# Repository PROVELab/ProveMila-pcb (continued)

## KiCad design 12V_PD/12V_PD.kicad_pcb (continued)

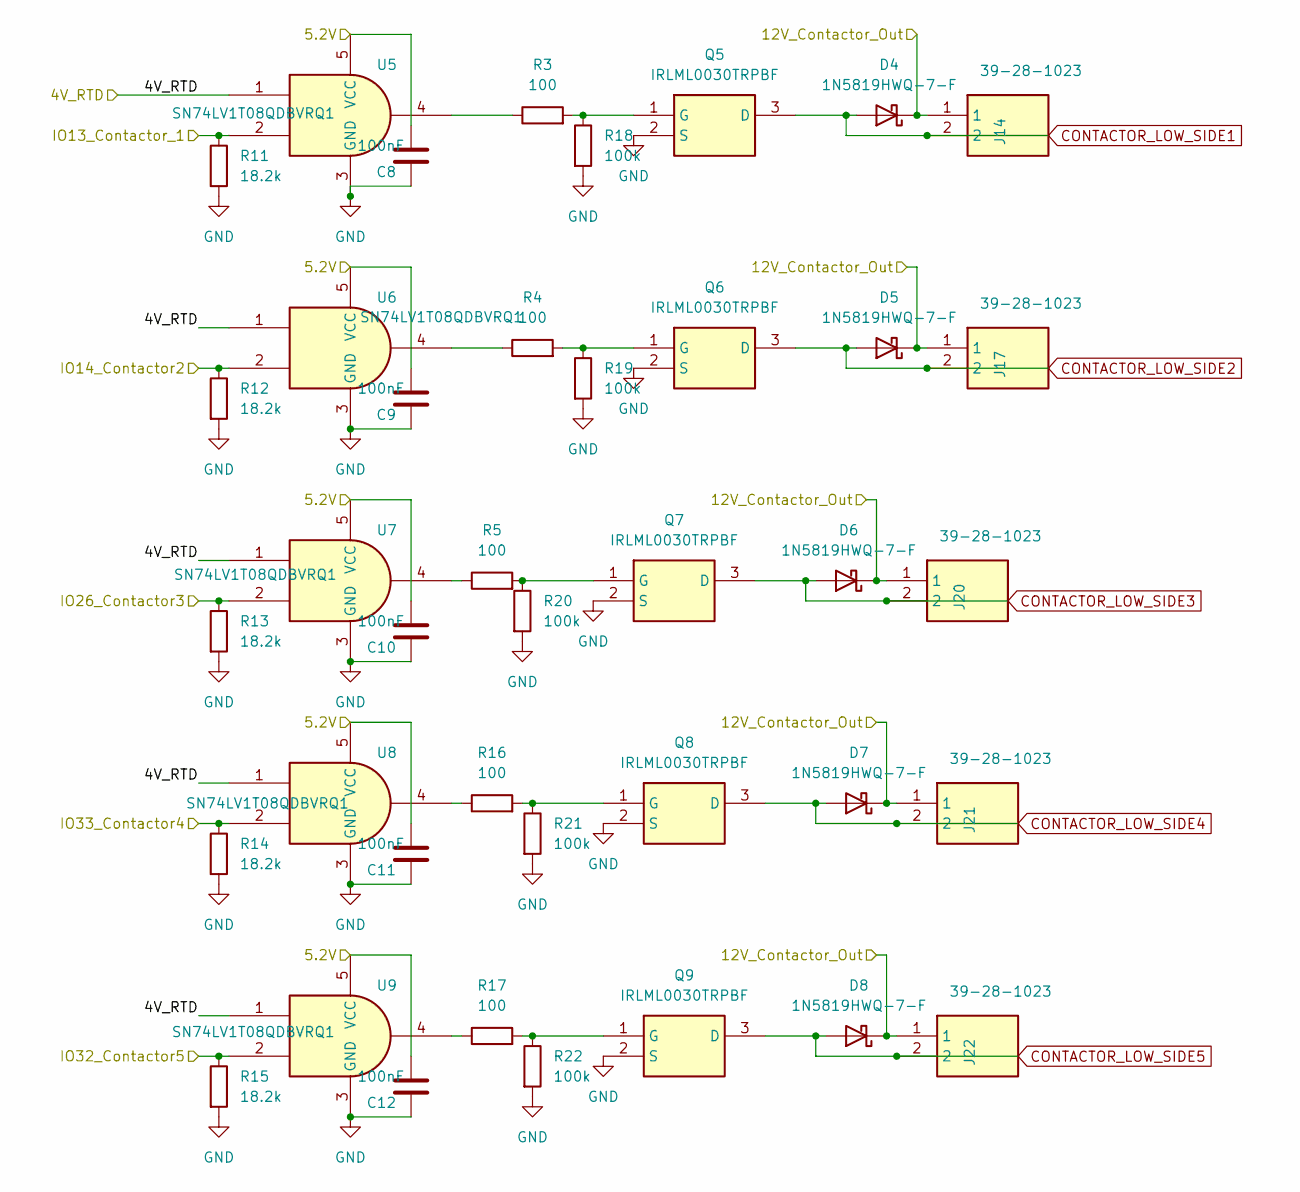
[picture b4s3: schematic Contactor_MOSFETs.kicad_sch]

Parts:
C8, C9, C10, C11, C12: 100nF; C_0805_2012Metric_Pad1.18x1.45mm_HandSolder
D4, D5, D6, D7, D8: 1N5819HWQ-7-F; D_SOD-123
J14, J17, J20, J21, J22: 39-28-1023; Mouser Part Number 538-39-28-1023
Q5, Q6, Q7, Q8, Q9: IRLML0030TRPBF; SOT-23-3; Mouser Part Number 942-IRLML0030TRPBF
R3, R4, R5, R16, R17: 100; R_0805_2012Metric_Pad1.20x1.40mm_HandSolder
R11, R12, R13, R14, R15: 18.2k; R_0805_2012Metric_Pad1.20x1.40mm_HandSolder
R18, R19, R20, R21, R22: 100k; R_0805_2012Metric_Pad1.20x1.40mm_HandSolder
U5, U6, U7, U8, U9: SN74LV1T08QDBVRQ1; SOT-23-5_HandSoldering

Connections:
/4V_RTD: U5.1, U6.1, U7.1, U8.1, U9.1; also elsewhere on the board
/12V: D4.1 (K), D5.1 (K), D6.1 (K), D7.1 (K), D8.1 (K), J14.1, J17.1, J20.1, J21.1, J22.1; also elsewhere on the board
/BUCK_5V: C8.1, C9.1, C10.1, C11.1, C12.1, U5.5 (VCC), U6.5 (VCC), U7.5 (VCC), U8.5 (VCC), U9.5 (VCC); also elsewhere on the board
/Contactor_MOSFETs/IO13_Contactor_1: R11.1, U5.2; also elsewhere on the board
/Contactor_MOSFETs/IO14_Contactor2: R12.1, U6.2; also elsewhere on the board
/Contactor_MOSFETs/IO26_Contactor3: R13.1, U7.2; also elsewhere on the board
/Contactor_MOSFETs/IO32_Contactor5: R15.1, U9.2; also elsewhere on the board
/Contactor_MOSFETs/IO33_Contactor4: R14.1, U8.2; also elsewhere on the board
CONTACTOR_LOW_SIDE1: D4.2 (A), J14.2, Q5.3 (D)
CONTACTOR_LOW_SIDE2: D5.2 (A), J17.2, Q6.3 (D)
CONTACTOR_LOW_SIDE3: D6.2 (A), J20.2, Q7.3 (D)
CONTACTOR_LOW_SIDE4: D7.2 (A), J21.2, Q8.3 (D)
CONTACTOR_LOW_SIDE5: D8.2 (A), J22.2, Q9.3 (D)
GND: C8.2, C9.2, C10.2, C11.2, C12.2, Q5.2 (S), Q6.2 (S), Q7.2 (S), Q8.2 (S), Q9.2 (S), R11.2, R12.2, R13.2, R14.2, R15.2, R18.2, R19.2, R20.2, R21.2, R22.2, U5.3 (GND), U6.3 (GND), U7.3 (GND), U8.3 (GND), U9.3 (GND); also elsewhere on the board
unnamed: Q5.1 (G), R3.2, R18.1
unnamed: Q6.1 (G), R4.2, R19.1
unnamed: Q7.1 (G), R5.2, R20.1
unnamed: Q8.1 (G), R16.2, R21.1
unnamed: Q9.1 (G), R17.2, R22.1
unnamed: R3.1, U5.4
unnamed: R4.1, U6.4
unnamed: R5.1, U7.4
unnamed: R16.1, U8.4
unnamed: R17.1, U9.4

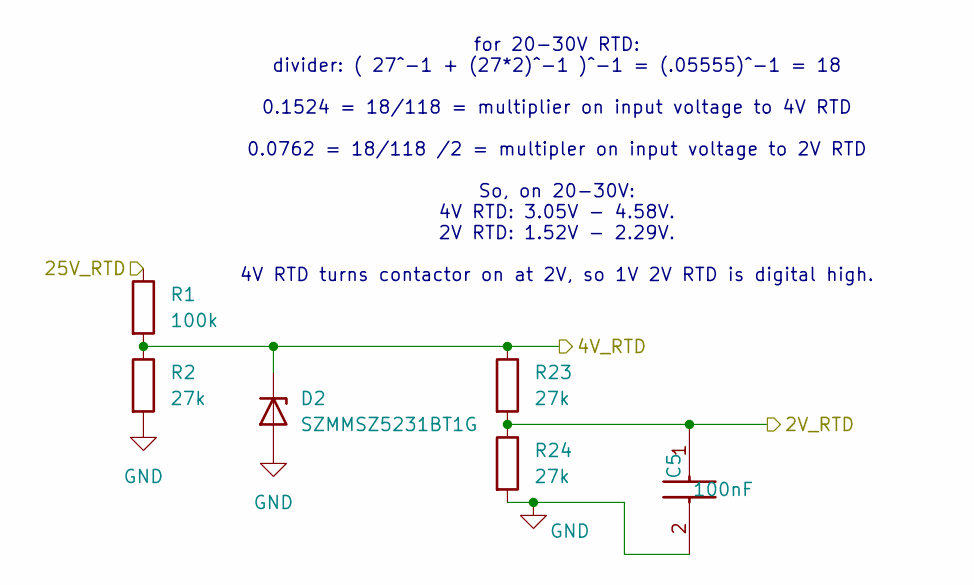
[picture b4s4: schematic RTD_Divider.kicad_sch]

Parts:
C5: 100nF; C_0805_2012Metric_Pad1.18x1.45mm_HandSolder
D2: SZMMSZ5231BT1G; D_SOD-123
R1: 100k; R_0805_2012Metric_Pad1.20x1.40mm_HandSolder
R2, R23, R24: 27k; R_0805_2012Metric_Pad1.20x1.40mm_HandSolder

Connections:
/4V_RTD: D2.1 (K), R1.2, R2.1, R23.1; also elsewhere on the board
/25V_RTD: R1.1; also elsewhere on the board
/RTD_Divider/2V_RTD: C5.1, R23.2, R24.1; also elsewhere on the board
GND: C5.2, D2.2 (A), R2.2, R24.2; also elsewhere on the board

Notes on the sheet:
for 20-30V RTD: divider: ( 27^-1 + (27*2)^-1 )^-1 = (.05555)^-1 = 18 0.1524 = 18/118 = multiplier on input voltage to 4V RTD 0.0762 = 18/118 /2 = multipler on input voltage to 2V RTD So, on 20-30V: 4V RTD: 3.05V - 4.58V. 2V RTD: 1.52V - 2.29V. 4V RTD turns contactor on at 2V, so 1V 2V RTD is digita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

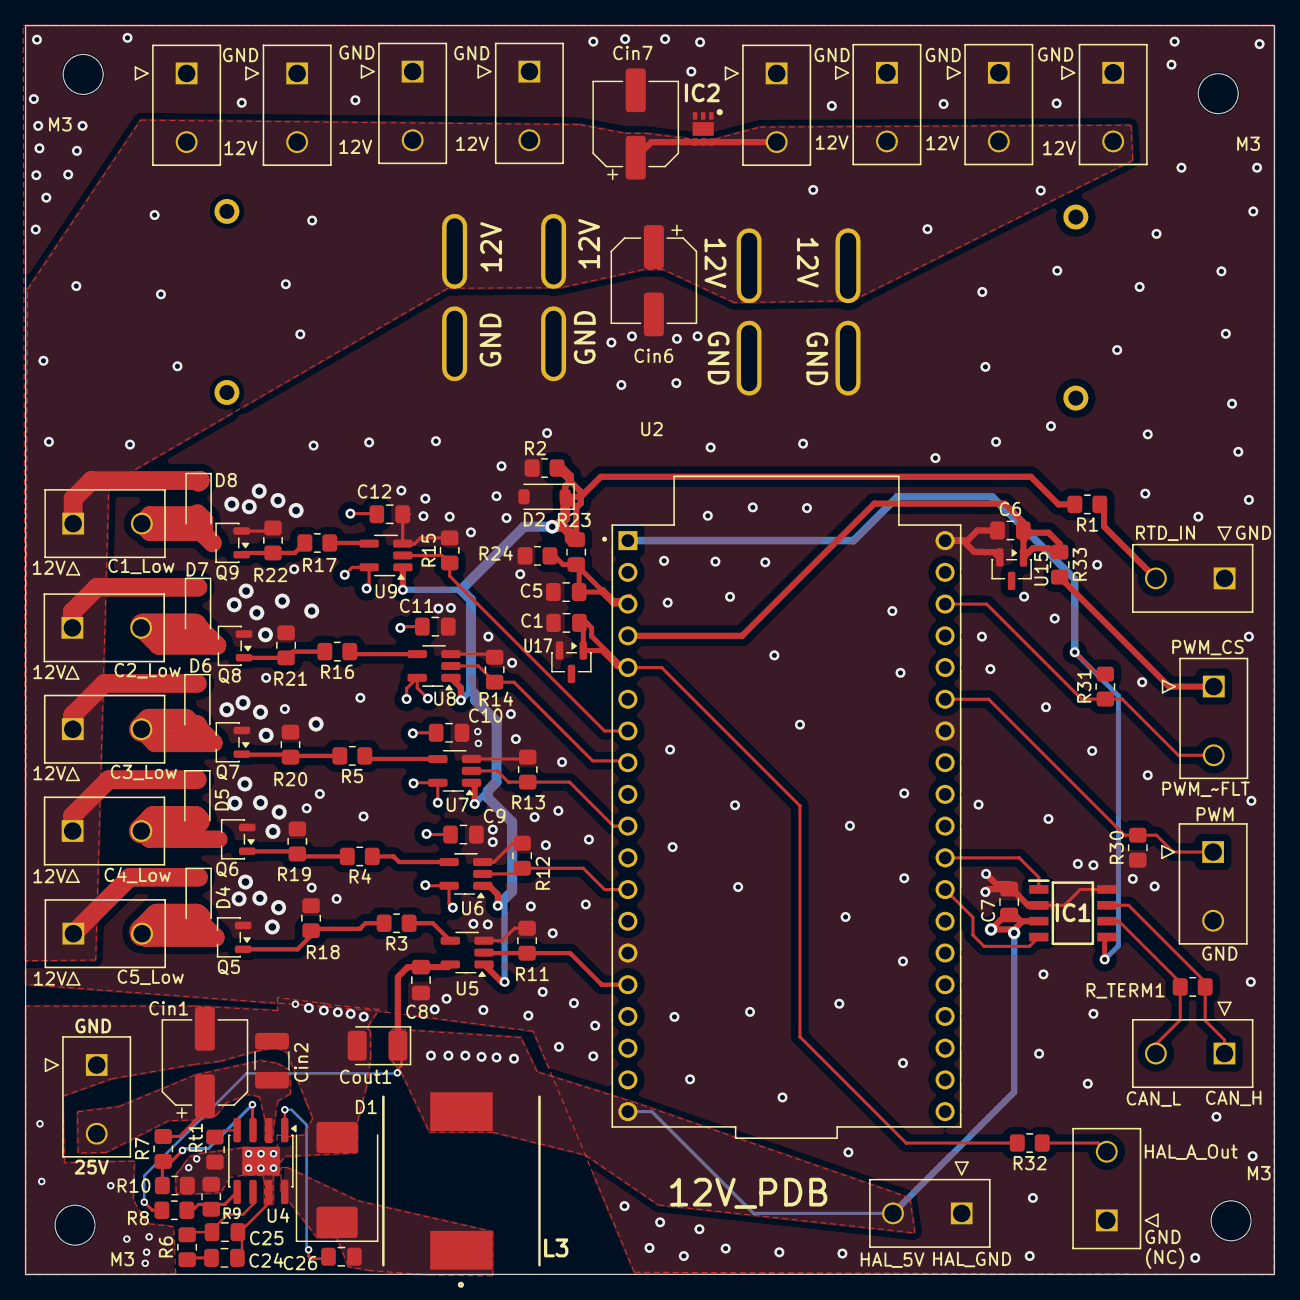
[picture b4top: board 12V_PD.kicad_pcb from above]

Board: 4 copper layers, 100.0 x 100.0 mm, 97 parts (0 on the bottom side), 45 nets.

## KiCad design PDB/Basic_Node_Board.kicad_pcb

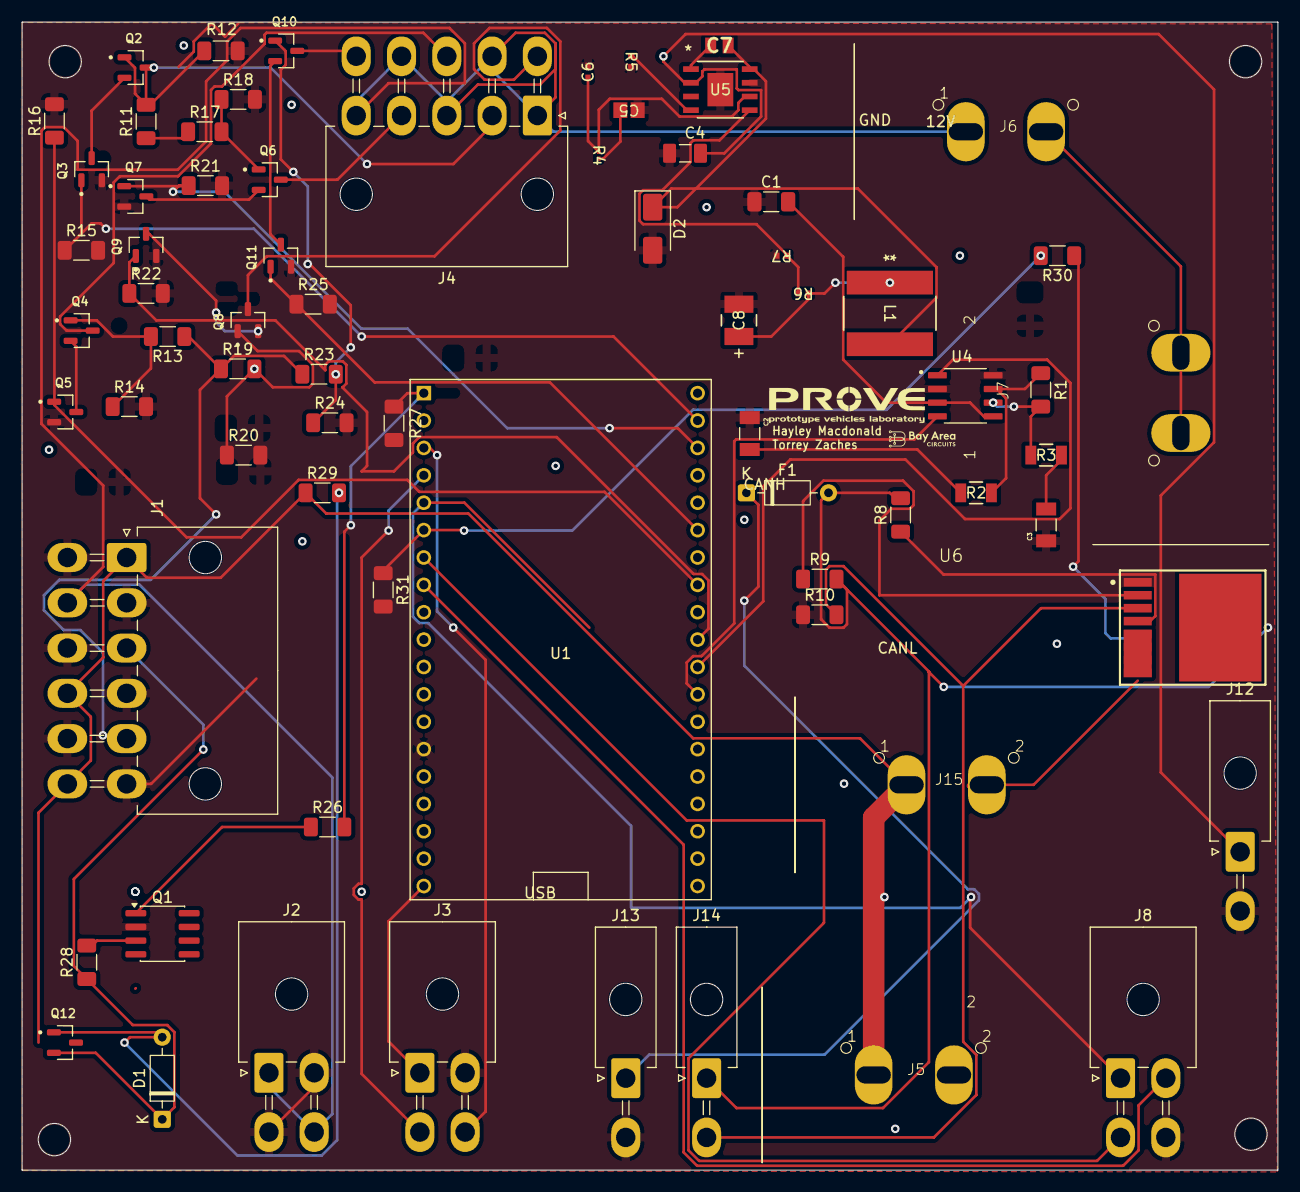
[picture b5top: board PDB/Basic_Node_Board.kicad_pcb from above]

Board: 2 copper layers, 116.5 x 106.5 mm, 71 parts (0 on the bottom side), 56 nets.

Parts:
C1: 0.1u; C_1206_3216Metric_Pad1.33x1.80mm_HandSolder
C2, C3: 30p; CAPC3216X170N
C4: 4.7 uF; CAPC3216X90N
C5: 12 nF; CAPC220145_88N_KEM
C6: 10 pF; CAP_CL05_SAM
C7: 100 nF; CAPC2012X94N
C8: 47uF; PCAP_TPE_B2_PAN
D1: D_Zener; D_DO-35_SOD27_P7.62mm_Horizontal
D2: SS34; D_SMA
F1: Fuse; D_DO-35_SOD27_P7.62mm_Horizontal
J1: EXT_CONNECTIONS; Molex_Mini-Fit_Jr_5569-12A2_2x06_P4.20mm_Horizontal
J2: EXT_BMS_MISC; Molex_Mini-Fit_Jr_5569-04A2_2x02_P4.20mm_Horizontal
J3: EXT_CURRENT_SENSOR; Molex_Mini-Fit_Jr_5569-04A2_2x02_P4.20mm_Horizontal
J4: Conn_02x05_Counter_Clockwise; Molex_Mini-Fit_Jr_5569-10A2_2x05_P4.20mm_Horizontal
J5: MOTOR_INVERTER_A; Anderson_1336G1_RightAngle_2Pin
J6: EXT12V_TO_BOARD; Anderson_1336G1_RightAngle_2Pin
J7: HBRIDGE_A; Anderson_1336G1_RightAngle_2Pin
J8: HBRIDGE; Molex_Mini-Fit_Jr_5569-04A2_2x02_P4.20mm_Horizontal
J12: Conn_01x02; Molex_Mini-Fit_Jr_5569-02A2_2x01_P4.20mm_Horizontal
J13: BATTERY_IN; Molex_Mini-Fit_Jr_5569-02A2_2x01_P4.20mm_Horizontal
J14: DASH_SWITCH; Molex_Mini-Fit_Jr_5569-02A2_2x01_P4.20mm_Horizontal
J15: 24V_TO_STEPDOWN; Anderson_1336G1_RightAngle_2Pin
L1: 27 uH; IND_BOURNS_SRN8040
Q1: Q_PMOS_GSD; SOIC-8_3.9x4.9mm_P1.27mm
Q2, Q3, Q4, Q5, Q6, Q7, Q8, Q9, Q10, Q11, Q12: IRLML0030TRPBF-1; SOT95P237X112-3N
R1: 120; R_1206_3216Metric_Pad1.30x1.75mm_HandSolder
R2, R3: 0; STA_RMCF1206_STP
R4: 15.4k; RES_RC0201_YAG
R5: 147k; RES_CRCW_0402
R6: 61.9k; RES_CRCW_0402
R7: CRCW0402118KFKED; RES_CRCW_0402
R8, R10, R11, R12, R13, R14, R15, R16, R17, R18, R19, R20, R21, R22, R23, R24, R25: 10k; R_1206_3216Metric_Pad1.30x1.75mm_HandSolder
R9: 2k; R_1206_3216Metric_Pad1.30x1.75mm_HandSolder
R26, R27: 100; R_1206_3216Metric_Pad1.30x1.75mm_HandSolder
R28, R29, R30: 100k; R_1206_3216Metric_Pad1.30x1.75mm_HandSolder
R31: 12k; R_1206_3216Metric_Pad1.30x1.75mm_HandSolder
U1: ESP32-DEVKITC
U4: TJA1050T_CM_118; SOIC127P600X175-8N
U5: TPS54560BQDDARQ1
U6: BTH50030-1LUA; IFX-PG-HSOF-8-6-V

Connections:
3V3_ESP: R26.2, R27.1, U1.1 (3V3)
5.3V OUT: C8.1, L1.1, R6.1
12V_IN: J1.8, J2.1, J2.4, J4.1, J4.3, J4.5, J4.7, J4.9, J6.1, J7.1
24V_FROM_RTD_PCB: J1.5, R11.1, R13.1, R17.1, R19.1, R23.1
24V_SWITCHED: J1.1, J1.10, J1.12, J5.1, J15.1, Q12.3, R29.1, R30.1, U6.5 (OUT1), U6.6 (OUT2), U6.7 (OUT3), U6.8 (OUT4)
24V_TO_RTD_PCB: D1.1 (K), J1.3, Q12.2, R28.1
/24V to 5.3V Converter/24V: C4.2, J12.1, U5.2 (VIN)
/Microcontroller/BUCK_5V: C1.2, U4.3 (VCC), U4.5 (VREF)
/Microcontroller/CANH: C2.2, R2.1
/Switch/24V_BATT: F1.1, J13.1
/Switch/24V_FUSED: F1.2, J14.1, R8.2, R9.2, U6.9 (VS)
/Switch/MAIN_EN: J14.2, R10.2, U6.3 (IN)
BUCK_5.3V: J3.1, U1.19 (5V)
CONTACTOR_LOW_SIDE1: J4.2, Q2.3
CONTACTOR_LOW_SIDE2: J4.4, Q6.3
CONTACTOR_LOW_SIDE3: J4.10, Q10.3
CONTACTOR_LOW_SIDE4: J4.8, Q4.3
CONTACTOR_LOW_SIDE5: J4.6, Q8.3
CS_ESP_34: J8.1, U1.5 (GPIO34/AD6)
FLT_ESP_33: J8.2, U1.8 (GPIO33/AD5/TOUCH8)
GND: C1.1, C2.1, C3.1, C4.1, C5.1, C6.2, C8.2, D2.2 (A), J1.2, J1.4, J1.6, J1.7, J1.9, J1.11, J2.2, J2.3, J3.2, J8.4, J12.2, J13.2, Q1.2 (S), Q3.2, Q5.2, Q7.2, Q9.2, Q11.2, R5.2, R7.2, R10.1, R12.2, R14.2, R15.2, R16.2, R18.2, R20.2, R21.2, R22.2, R24.2, R25.2, R27.2, R31.2, U1.14 (GND1), U4.2 (GND), U4.8 (S), U5.7 (GND), U5.EPAD, U6.1 (GND)
IO18_CONTACTOR5: Q9.1, R22.1, U1.29 (GPIO5/SPI_SS)
IO19_CONTACTOR4: Q5.1, R16.1, U1.31 (GPIO19/SPI_MISO)
IO21_CONTACTOR3: Q11.1, R25.1, U1.33 (GPIO21/WIRE_SDA)
IO22_CONTACTOR2: Q7.1, R21.1, U1.36 (GPIO22/WIRE_SCL)
IO23_CONTACTOR1: Q3.1, R15.1, U1.37 (GPIO23/SPI_MOSI)
unnamed: C5.2, R4.2
unnamed: D1.2 (A), Q12.1, R29.2
unnamed: C7.1, D2.1 (K), L1.2, U5.8 (SW)
unnamed: U1.28 (GPIO17), U4.1 (TXD)
unnamed: U1.27 (GPIO16), U4.4 (RXD)
unnamed: C3.2, R3.2
unnamed: Q1.3 (D), R28.2
unnamed: Q1.1 (G), R26.1
unnamed: Q2.1, R11.2, R12.1
unnamed: Q2.2, Q3.3
unnamed: Q4.1, R13.2, R14.1
unnamed: Q4.2, Q5.3
unnamed: Q6.1, R17.2, R18.1
unnamed: Q6.2, Q7.3
unnamed: Q8.1, R19.2, R20.1
unnamed: Q8.2, Q9.3
unnamed: Q10.1, R23.2, R24.1
unnamed: Q10.2, Q11.3
unnamed: R1.1, R2.2, U4.7 (CANH)
unnamed: R1.2, R3.1, U4.6 (CANL)
unnamed: C7.2, U5.1 (BOOT)
unnamed: C6.1, R4.1, U5.6 (COMP)
unnamed: R6.2, R7.1, U5.5 (FB)
unnamed: R5.1, U5.4 (RT/CLK)
unnamed: R8.1, U6.4 (DEN)
unnamed: R9.1, U6.2 (IS)
PWM_ESP_32: J8.3, U1.7 (GPIO32/AD4/TOUCH9)
RTD_24V_SENSE_ADC: R30.2, R31.1, U1.6 (GPIO35/AD7)
VN_ESP: J3.3, U1.4 (GPIO39/AD3/SVN)
VP_ESP: J3.4, U1.3 (GPIO36/AD0/SVP)

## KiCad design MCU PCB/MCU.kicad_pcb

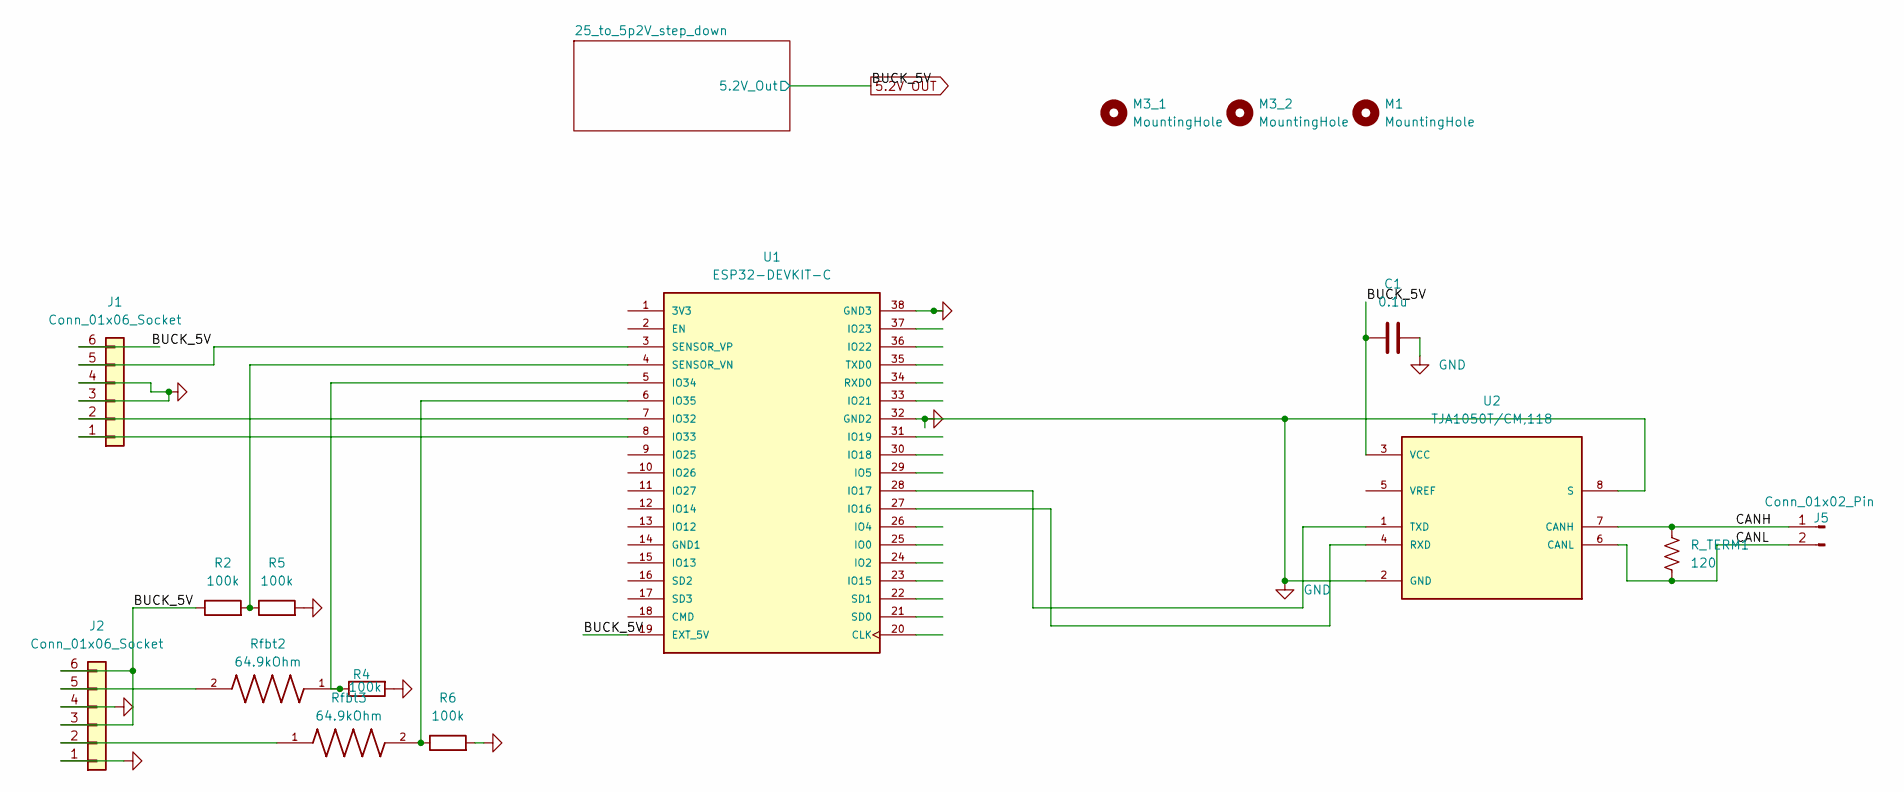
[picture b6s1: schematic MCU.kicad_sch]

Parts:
C1: 0.1u; C_1206_3216Metric_Pad1.33x1.80mm_HandSolder; MPN 1206B104K500CT
J1, J2: Conn_01x06_Socket; TE_1877285-6
J5: Conn_01x02_Pin; TE_1877285-2
M1, M3_1, M3_2: MountingHole; MountingHole_3.2mm_M3
R2, R4, R5, R6: 100k; R_1206_3216Metric_Pad1.30x1.75mm_HandSolder
R_TERM1: 120; R_1206_3216Metric_Pad1.30x1.75mm_HandSolder; MPN RMCF1206JT120R
Rfbt2, Rfbt3: 64.9kOhm; R_1206_3216Metric_Pad1.30x1.75mm_HandSolder
U1: ESP32-DEVKIT-C; MODULE_ESP32-DEVKITC; PARTREV N/A
U2: TJA1050T/CM,118; SOIC-8_3.9x4.9mm_P1.27mm; PARTREV 4

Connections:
5.2V OUT: C1.2, J1.6, J2.3, J2.6, R2.1, U1.19 (EXT_5V), U2.3 (VCC); also elsewhere on the board
/CANH: J5.1, R_TERM1.1, U2.7 (CANH)
/CANL: J5.2, R_TERM1.2, U2.6 (CANL)
GND: C1.1, J1.3, J1.4, J2.1, J2.4, R4.2, R5.2, R6.2, U1.32 (GND2), U1.38 (GND3), U2.2 (GND), U2.8 (S); also elsewhere on the board
unnamed: J1.1, U1.8 (IO33)
unnamed: J1.2, U1.7 (IO32)
unnamed: J1.5, U1.3 (SENSOR_VP)
unnamed: J2.2, Rfbt3.1
unnamed: J2.5, Rfbt2.2
unnamed: U1.27 (IO16), U2.4 (RXD)
unnamed: U1.28 (IO17), U2.1 (TXD)
unnamed: R4.1, Rfbt2.1, U1.5 (IO34)
unnamed: R6.1, Rfbt3.2, U1.6 (IO35)
unnamed: R2.2, R5.1, U1.4 (SENSOR_VN)

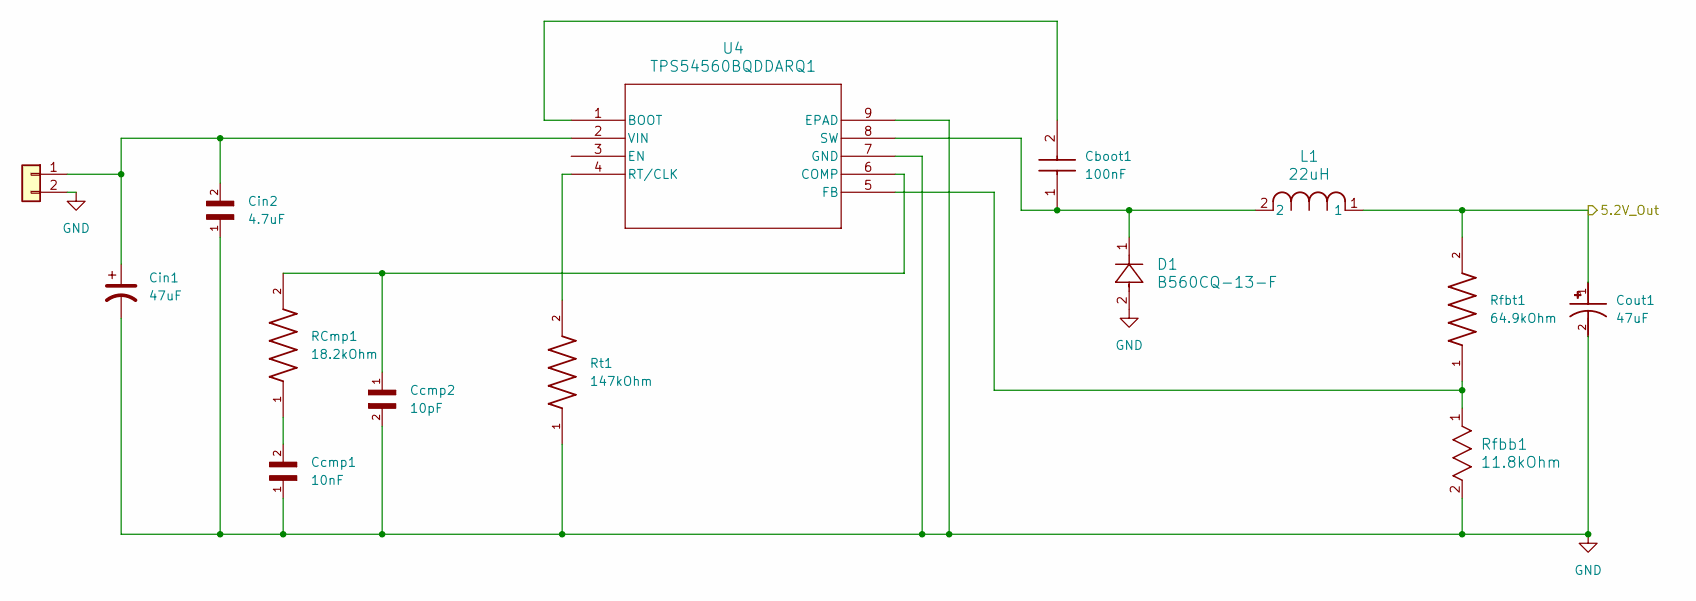
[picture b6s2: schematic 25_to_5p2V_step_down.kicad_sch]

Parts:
Cboot1: 100nF; C_1206_3216Metric_Pad1.33x1.80mm_HandSolder
Ccmp1: 10nF; C_1206_3216Metric_Pad1.33x1.80mm_HandSolder
Ccmp2: 10pF; C_1206_3216Metric_Pad1.33x1.80mm_HandSolder
Cin1: 47uF; CP_Elec_6.3x7.7
Cin2: 4.7uF; C_1206_3216Metric_Pad1.33x1.80mm_HandSolder
Cout1: 47uF; CP_EIA-3528-21_Kemet-B_HandSolder
D1: B560CQ-13-F; D_SMC
J3: Conn_01x02; TE_1877285-2
L1: 22uH; L_Bourns_SRP1245A
RCmp1: 18.2kOhm; R_1206_3216Metric_Pad1.30x1.75mm_HandSolder
Rfbb1: 11.8kOhm; R_1206_3216Metric_Pad1.30x1.75mm_HandSolder
Rfbt1: 64.9kOhm; R_1206_3216Metric_Pad1.30x1.75mm_HandSolder
Rt1: 147kOhm; R_1206_3216Metric_Pad1.30x1.75mm_HandSolder
U4: TPS54560BQDDARQ1; SOIC-8-1EP_3.9x4.9mm_P1.27mm_EP2.29x3mm

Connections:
5.2V OUT: Cout1.1, L1.1, Rfbt1.2; also elsewhere on the board
GND: Ccmp1.1, Ccmp2.2, Cin1.2, Cin2.1, Cout1.2, D1.2, J3.2, Rfbb1.2, Rt1.1, U4.7 (GND), U4.9 (EPAD); also elsewhere on the board
unnamed: Ccmp1.2, RCmp1.1
unnamed: Cin1.1, Cin2.2, J3.1, U4.2 (VIN)
unnamed: Cboot1.2, U4.1 (BOOT)
unnamed: Ccmp2.1, RCmp1.2, U4.6 (COMP)
unnamed: Rfbb1.1, Rfbt1.1, U4.5 (FB)
unnamed: Rt1.2, U4.4 (RT/CLK)
unnamed: Cboot1.1, D1.1, L1.2, U4.8 (SW)

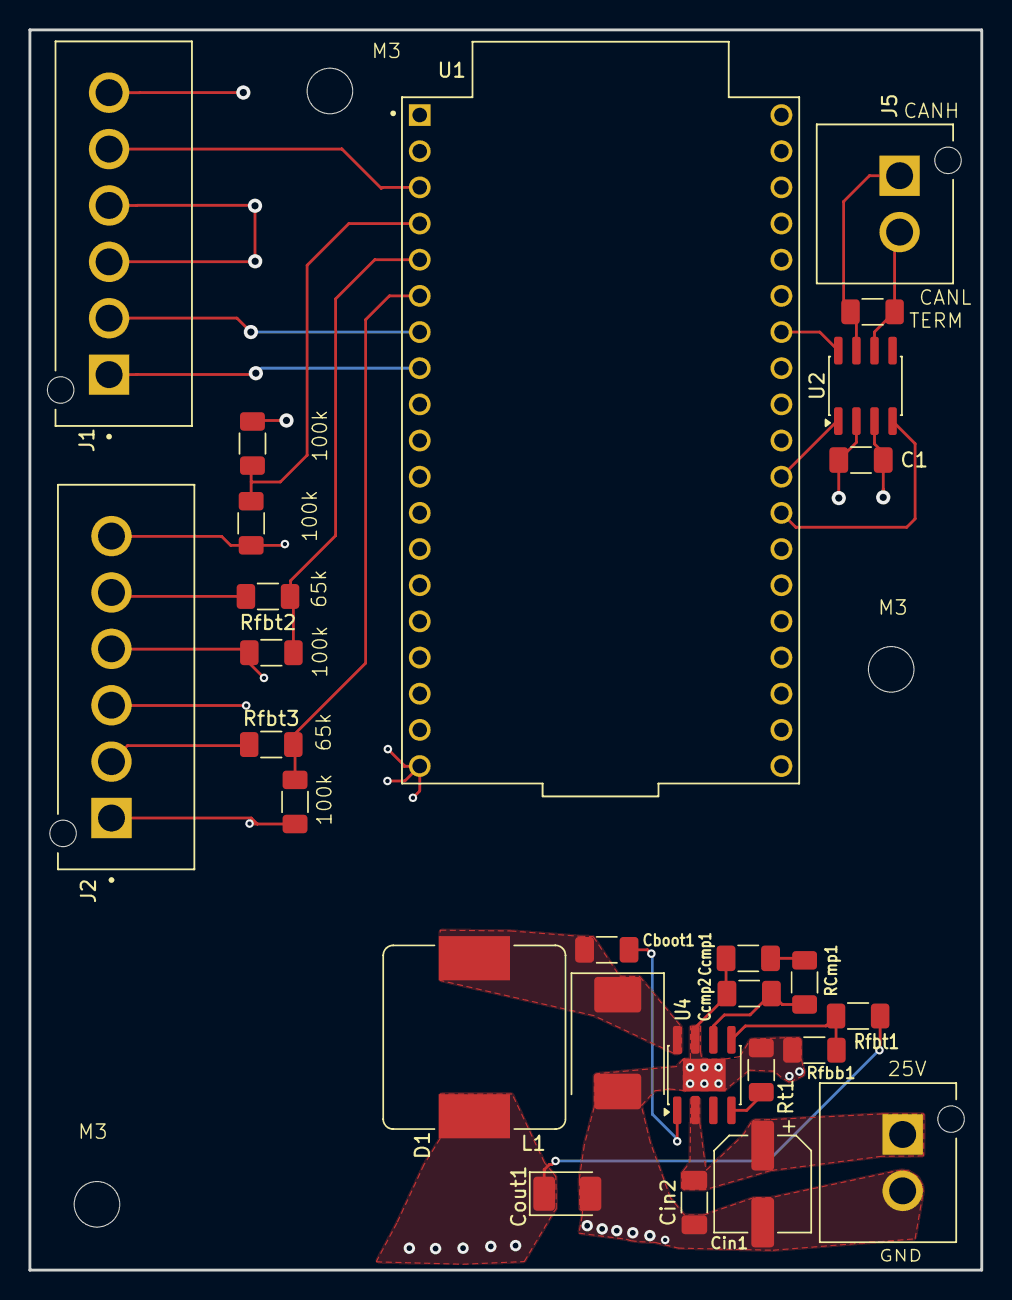
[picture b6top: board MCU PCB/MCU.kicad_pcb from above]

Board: 4 copper layers, 66.8 x 87.1 mm, 30 parts (0 on the bottom side), 21 nets.

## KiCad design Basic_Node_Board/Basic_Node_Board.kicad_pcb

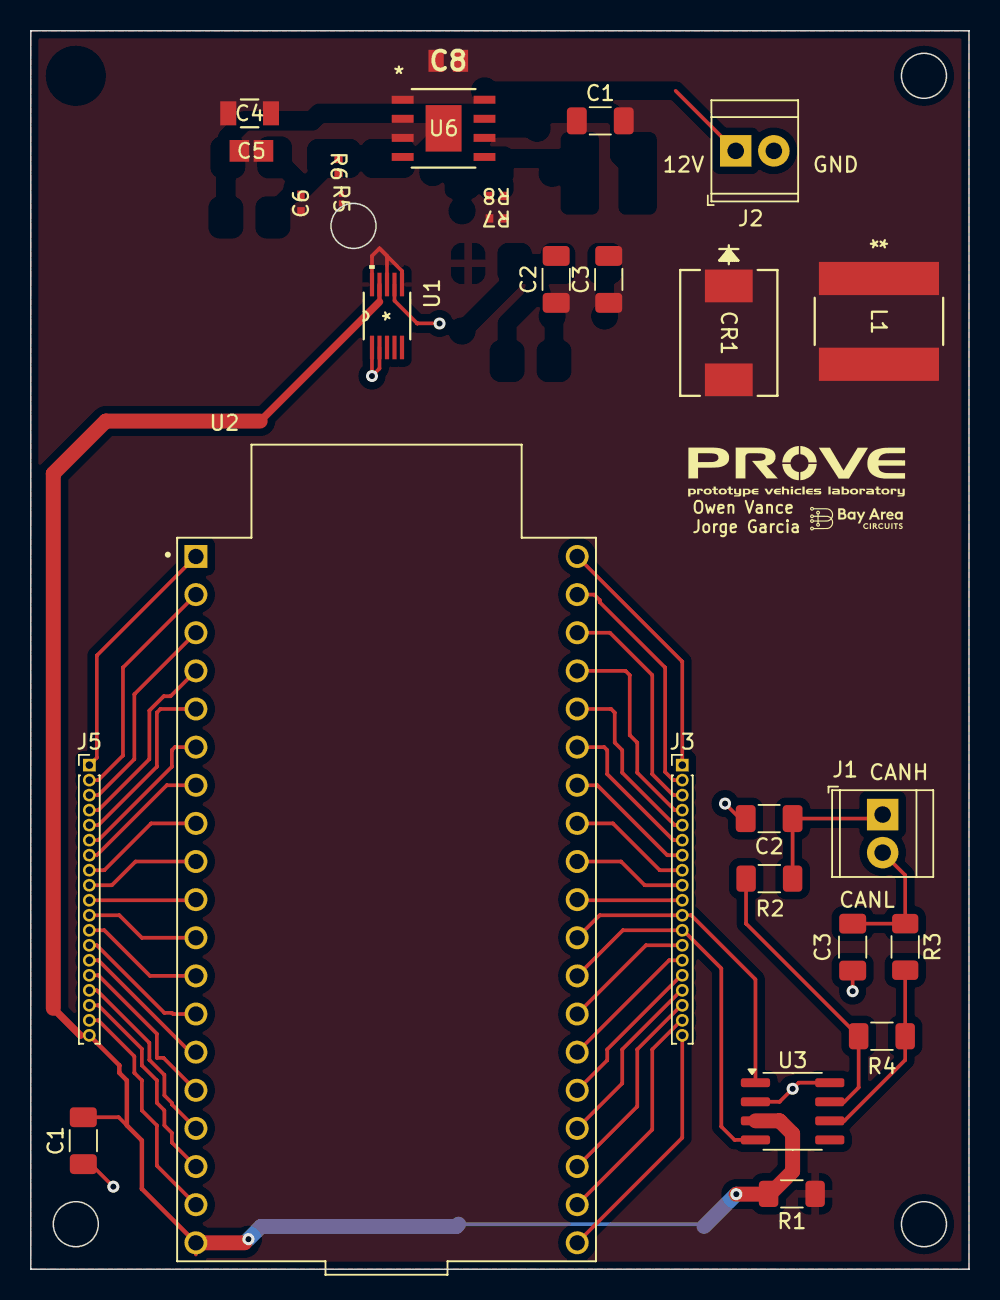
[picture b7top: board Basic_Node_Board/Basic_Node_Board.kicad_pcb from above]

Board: 2 copper layers, 62.5 x 82.5 mm, 28 parts (0 on the bottom side), 52 nets.

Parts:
C1, C1#2: 0.1u; C_1206_3216Metric_Pad1.33x1.80mm_HandSolder
C2, C2#2, C3, C3#2: 30p; C_1206_3216Metric_Pad1.33x1.80mm_HandSolder
C4: GRM31CR71H475KA12L; G-31_MUR
C5: C0805C122J5GACTU; CAPC220145_88N_KEM
C6: CL05C110JB5NNNC; CAP_CL05_SAM
C8: 08053C104KAT2A; CAPC2012X94N
CR1: B560C-13-F; SMC_DIO
J1: Conn_01x02_Pin; TerminalBlock_TE_282834-2_1x02_P2.54mm_Horizontal
J2: Conn_01x02; TerminalBlock_TE_282834-2_1x02_P2.54mm_Horizontal
J3, J5: Conn_01x19_Socket; PinHeader_1x19_P1.00mm_Vertical
L1: SRN8040-100M; IND_BOURNS_SRN8040
R1: 30m; R_1206_3216Metric_Pad1.30x1.75mm_HandSolder
R2, R3: 0; R_1206_3216Metric_Pad1.30x1.75mm_HandSolder
R4: 120; R_1206_3216Metric_Pad1.30x1.75mm_HandSolder
R5: RC0201FR-0723K7L; RES_RC0201_YAG
R6: CRCW0402118KFKED; RES_CRCW_0402
R7: CRCW040261K9FKED; RES_CRCW_0402
R8: CRCW040211K0FKED; RES_CRCW_0402
U1: INA220 Current Monitor; DGS10
U2: ESP32-DEVKIT-C; MODULE_ESP32-DEVKITC
U3: TJA1050T/CM,118; SOIC-8_3.9x4.9mm_P1.27mm
U6: TPS54560BQDDARQ1

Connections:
5.3V OUT: L1.1, R7.1
+5V: R1.1, U1.6 (VS), U1.8 (VBUS), U1.10 (VIN+)
+5VD: C1.2, J5.19, R1.2, U1.9 (VIN-), U2.19 (EXT_5V), U3.3 (VCC)
/24V to 5.3V Converter/24V: C4.2, U6.2 (VIN)
/Microcontroller/CANH: C2.1, C2#2.1, J1.1, R2.1
/Microcontroller/CANL: C3.1, C3#2.1, J1.2, R3.1
BUCK_GND: C1#2.1, C2#2.2, C3#2.2, C4.1, C5.1, C6.2, CR1.2, R6.1, R8.1, U6.7 (GND), U6.EPAD
GND: C1.1, C2.2, C3.2, J2.2, J5.14, U1.1 (A1), U1.2 (A0), U1.7 (GND), U2.14 (GND1), U3.2 (GND), U3.8 (S)
unnamed: C5.2, R5.1
unnamed: J3.1, U2.38 (GND3)
unnamed: J3.2, U2.37 (IO23)
unnamed: J3.3, U2.36 (IO22)
unnamed: J3.4, U2.35 (TXD0)
unnamed: J3.5, U2.34 (RXD0)
unnamed: J3.6, U2.33 (IO21)
unnamed: J3.7, U2.32 (GND2)
unnamed: J3.8, U2.31 (IO19)
unnamed: J3.9, U2.30 (IO18)
unnamed: J3.10, U2.29 (IO5)
unnamed: J3.11, U2.28 (IO17), U3.1 (TXD)
unnamed: J3.12, U2.27 (IO16), U3.4 (RXD)
unnamed: J3.13, U2.26 (IO4)
unnamed: J3.14, U2.25 (IO0)
unnamed: J3.15, U2.24 (IO2)
unnamed: J3.16, U2.23 (IO15)
unnamed: J3.17, U2.22 (SD1)
unnamed: J3.18, U2.21 (SD0)
unnamed: J3.19, U2.20 (CLK)
unnamed: J5.1, U2.1 (3V3)
unnamed: J5.2, U2.2 (EN)
unnamed: J5.3, U2.3 (SENSOR_VP)
unnamed: J5.4, U2.4 (SENSOR_VN)
unnamed: J5.5, U2.5 (IO34)
unnamed: J5.6, U2.6 (IO35)
unnamed: J5.7, U2.7 (IO32)
unnamed: J5.8, U2.8 (IO33)
unnamed: J5.9, U2.9 (IO25)
unnamed: J5.10, U2.10 (IO26)
unnamed: J5.11, U2.11 (IO27)
unnamed: J5.12, U2.12 (IO14)
unnamed: J5.13, U2.13 (IO12)
unnamed: J5.15, U2.15 (IO13)
unnamed: J5.16, U2.16 (SD2)
unnamed: J5.17, U2.17 (SD3)
unnamed: J5.18, U2.18 (CMD)
unnamed: R2.2, R4.1, U3.7 (CANH)
unnamed: R3.2, R4.2, U3.6 (CANL)
unnamed: C8.2, U6.1 (BOOT)
unnamed: C6.1, R5.2, U6.6 (COMP)
unnamed: R7.2, R8.2, U6.5 (FB)
unnamed: R6.2, U6.4 (RT/CLK)
unnamed: C8.1, CR1.1, L1.2, U6.8 (SW)

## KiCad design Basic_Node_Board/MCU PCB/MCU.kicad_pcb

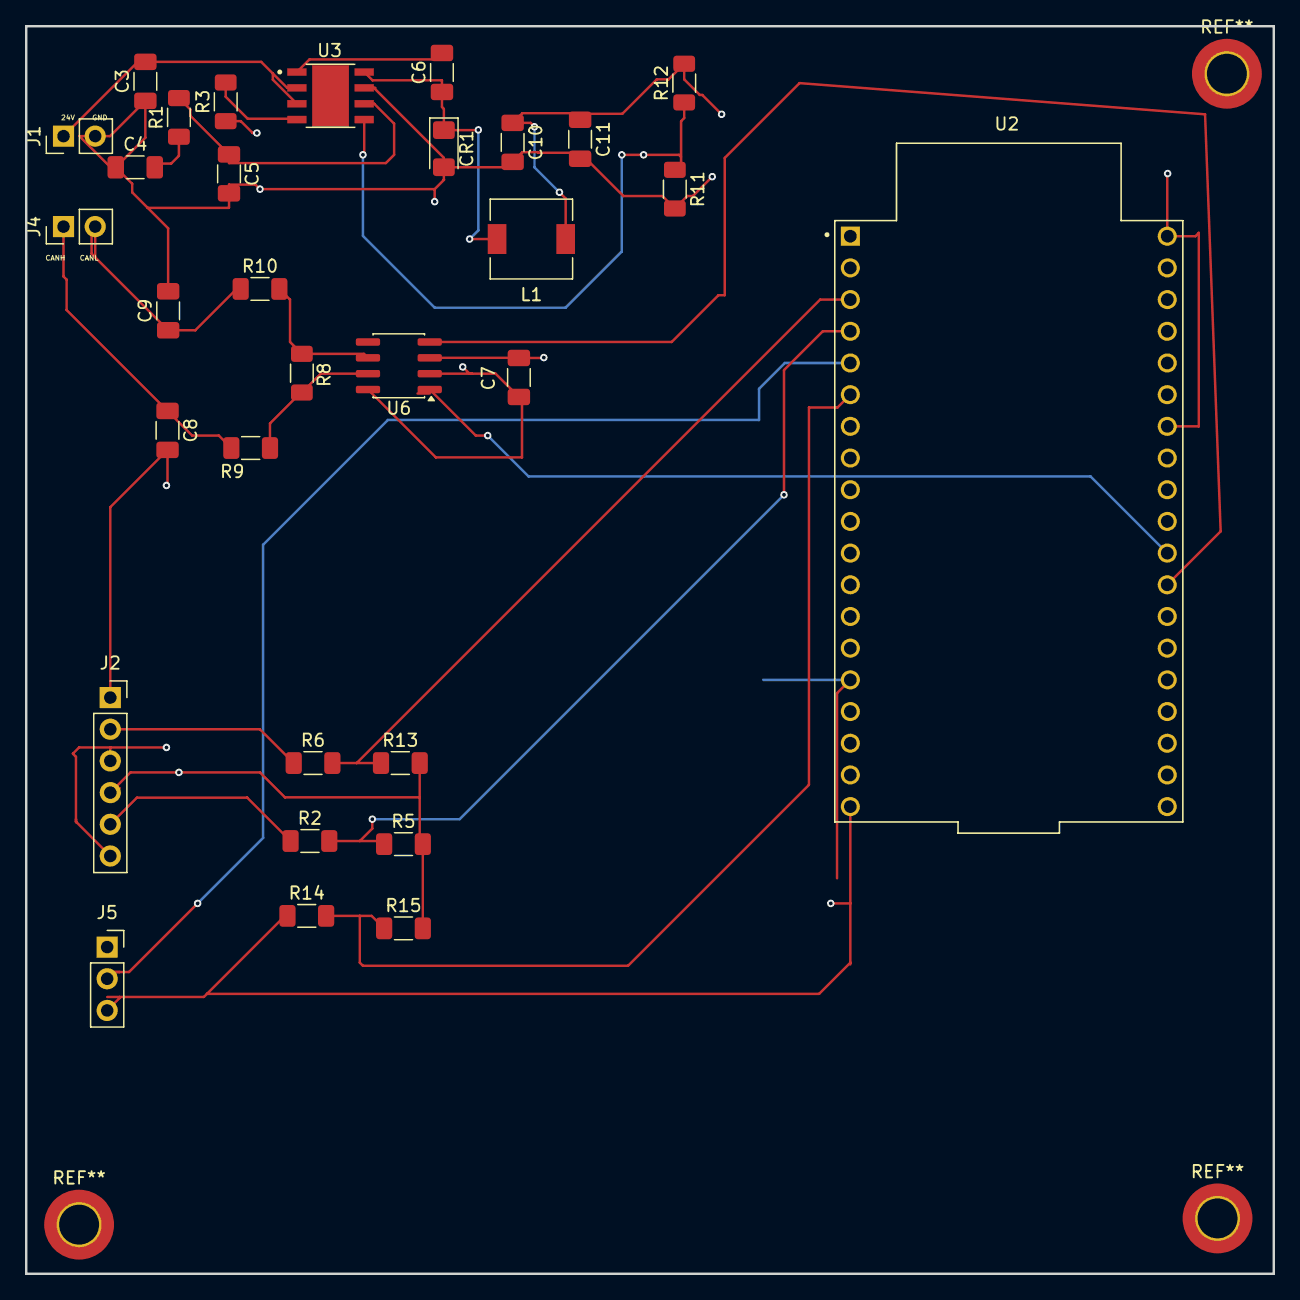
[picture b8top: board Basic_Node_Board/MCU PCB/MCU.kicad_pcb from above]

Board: 4 copper layers, 100.0 x 100.0 mm, 31 parts (0 on the bottom side), 21 nets.

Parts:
C3: 30uF; C_1206_3216Metric_Pad1.33x1.80mm_HandSolder
C4: 82nF; C_1206_3216Metric_Pad1.33x1.80mm_HandSolder
C5: 100pF; C_1206_3216Metric_Pad1.33x1.80mm_HandSolder
C6: 100nF; C_1206_3216Metric_Pad1.33x1.80mm_HandSolder
C7: 0.1u; C_1206_3216Metric_Pad1.33x1.80mm_HandSolder
C8, C9: 30p; C_1206_3216Metric_Pad1.33x1.80mm_HandSolder
C10, C11: 47uF; C_1206_3216Metric_Pad1.33x1.80mm_HandSolder
CR1: SS34; D_1206_3216Metric_Pad1.42x1.75mm_HandSolder
J1: Conn_01x02; PinHeader_1x02_P2.54mm_Vertical
J2: Conn_01x06_Socket; PinSocket_1x06_P2.54mm_Vertical
J4: Conn_01x02_Pin; PinHeader_1x02_P2.54mm_Vertical
J5: Conn_01x03_Socket; PinSocket_1x03_P2.54mm_Vertical
L1: 47uH; L_6.3x6.3_H3
R1: 5.1k; R_1206_3216Metric_Pad1.30x1.75mm_HandSolder
R2, R5, R6, R13, R14, R15: 100k; R_1206_3216Metric_Pad1.30x1.75mm_HandSolder
R3: 243k; R_1206_3216Metric_Pad1.30x1.75mm_HandSolder
R8: 120; R_1206_3216Metric_Pad1.30x1.75mm_HandSolder
R9, R10: 0; R_1206_3216Metric_Pad1.30x1.75mm_HandSolder
R11: 10k; R_1206_3216Metric_Pad1.30x1.75mm_HandSolder
R12: 56.2k; R_1206_3216Metric_Pad1.30x1.75mm_HandSolder
U2: ESP32-DEVKIT-C; MODULE_ESP32-DEVKITC
U3: TPS54560BQDDARQ1; VREG_LM5017MR_NOPB
U6: TJA1050T/CM,118; SOIC-8_3.9x4.9mm_P1.27mm

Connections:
5.3V OUT: C7.2, C10.1, C11.1, J2.3, J2.6, J5.3, L1.1, R12.2, R14.1, U2.19 (EXT_5V), U6.3 (VCC)
/24V: C3.2, J1.1, U3.2 (VIN), U3.3 (EN)
/CANH: C8.1, J4.1, R9.1
/CANL: C9.1, J4.2, R10.1
GND: C3.1, C4.1, C5.2, C7.1, C8.2, C9.2, C10.2, C11.2, CR1.2, J1.2, J2.1, J2.4, J5.1, R3.1, R5.2, R11.2, R13.2, R15.2, U2.32 (GND2), U2.38 (GND3), U3.7 (GND), U6.2 (GND), U6.8 (S)
unnamed: C4.2, R1.1
unnamed: J2.2, R6.1
unnamed: J2.5, R2.1
unnamed: U2.28 (IO17), U6.1 (TXD)
unnamed: U2.27 (IO16), U6.4 (RXD)
unnamed: J5.2, U2.5 (IO34)
unnamed: R14.2, R15.1, U2.6 (IO35)
unnamed: R2.2, R5.1, U2.4 (SENSOR_VN)
unnamed: R6.2, R13.1, U2.3 (SENSOR_VP)
unnamed: C6.2, U3.1 (BOOT)
unnamed: C5.1, R1.2, U3.6 (COMP)
unnamed: R11.1, R12.1, U3.5 (FB)
unnamed: R3.2, U3.4 (RT/CLK)
unnamed: C6.1, CR1.1, L1.2, U3.8 (SW)
unnamed: R8.1, R9.2, U6.7 (CANH)
unnamed: R8.2, R10.2, U6.6 (CANL)

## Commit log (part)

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2024-02-24 Backlink to CADLAB.io has been added.
2024-03-04 Basic node board layout
2024-04-24 Add INA220 current sensor to schematic
2024-04-27 Update schematics to use PROVE HTTP lib
2024-05-01 current sensor schematic added
2024-05-01 updated load symbol
2024-10-10 Update ProveMila-partslib for UART-USBC-Dock
2024-10-16 Add USBC_UART_Dock_Prototype Project
2024-10-22 Rev. A ready for review
2024-10-30 Add TJA1050 symbol
2024-10-31 Add ESP32 to library
2024-11-08 Rev1 CAN Sensor board
    Edits done in microcontroller subfile - added can transciever, passive components and sockets and whatnot. waiting for buck to be added with the current sensor subfile
2024-11-15 mh_initial_node_board_edits
2024-11-15 Add AP64040 buck IC
2024-11-15 Add power supply components
2024-11-18 Update PROVE parts lib
2024-11-19 Update symbols table
2024-11-19 Ready for DFM
2024-12-04 Add BAC logo
2024-12-04 Update partslib BAC logo
2025-01-10 Update symbol AP640 library
2025-01-16 Update partslib
2025-03-09 Initial PCB design for sensor board
2025-05-08 owens basic node
2025-05-08 Added full project
2026-02-07 added sd card, dividers, and connector
2026-02-24 Add files via upload
    Basic Node Board with IMU on the board (Updated PCB Schematic is under the files with the date attached)
2026-03-07 Adding Buck Converter Schematic/Footprints
    Added footprints to main pcb. Removing duplicate footprints (might cause problems, we will find out).
2026-03-09 updated schematic to match diagram
2026-03-10 initial pcb board with transciever, esp32 and can transceiver
2026-03-14 schematic done before layout
2026-04-08 microcontroller board without the buck converter yet
2026-04-08 add buck buck converter step down to the pcb (not wirted yet)
2026-04-16 beta test with all connections for final pcb layout - JK
2026-04-18 revised e22P transceiver module footprint and began to add labels for the 3d Board design
2026-04-25 fixed routing under the lora board module
2026-04-25 small revisions before printing
2026-04-25 verified all componnents are 1206 for SMD
2026-04-25 reverified pin headers for canbus and power
2026-05-02 breif mockup of the mcu board
2026-05-13 made changes to some footprints and overall layout of the board (in line with TI buck recomendations)
2026-05-27 fixed the buck converter
2026-05-30 Power Distribution PCB KiCAD Schematic
2026-05-30 Julia's IMU PCB (Incomplete)
    PCB with 24-5V buck converter, CAN Transceiver, ESP, thermal resistor connector, humidity sensor, SDIO breakout board, Adafruit ICM breakout board.
    *******INCOMPLETE DESIGN*******
    Capacitances for the buck converter and J1 and J4 connectors are INCORRECT, need to be adjusted before ordering.
2026-06-01 changed values for buck converter - Jacob K
2026-06-01 made changes to buck converter - jacob Kyeyune
2026-06-03 made fixes to the buck converter
2026-06-22 fixed the pin and connectors for the mcu board
